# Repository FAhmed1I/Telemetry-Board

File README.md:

Telemetry Tracking PCB for automotive applications. Designed for testing of automotive projects

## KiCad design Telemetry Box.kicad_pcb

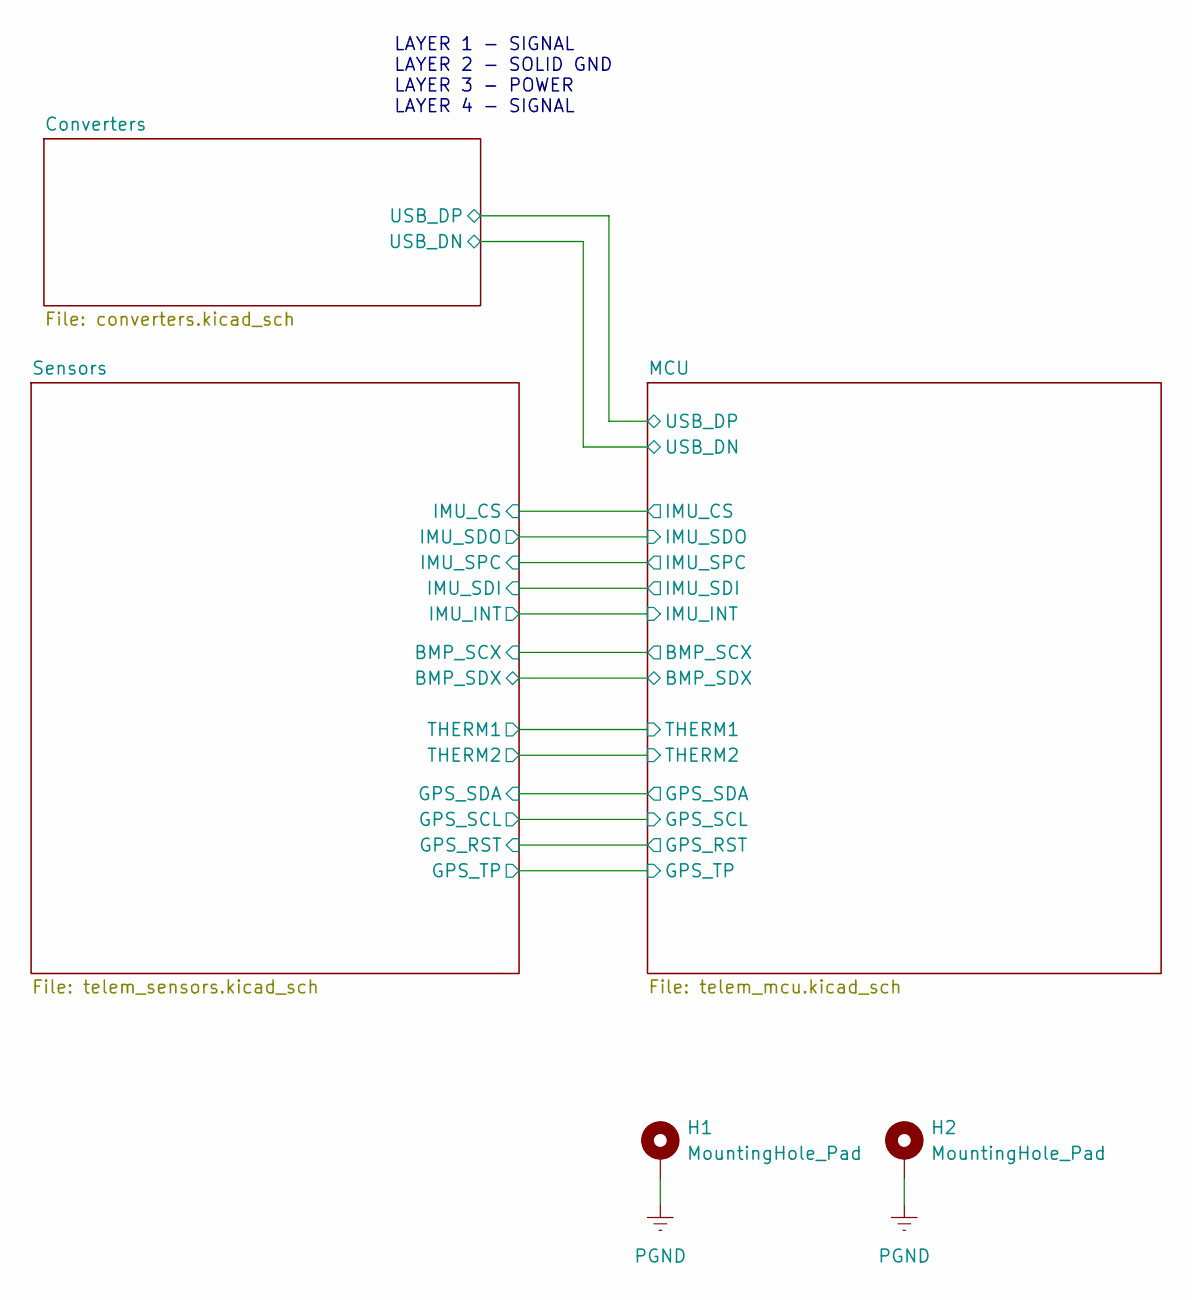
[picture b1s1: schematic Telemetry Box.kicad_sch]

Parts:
H1, H2: MountingHole_Pad; MountingHole_2.2mm_M2_DIN965_Pad

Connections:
PGND: H1.1 (1_1), H2.1 (1_1); also elsewhere on the board

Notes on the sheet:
LAYER 1 - SIGNAL LAYER 2 - SOLID GND LAYER 3 - POWER LAYER 4 - SIGNAL

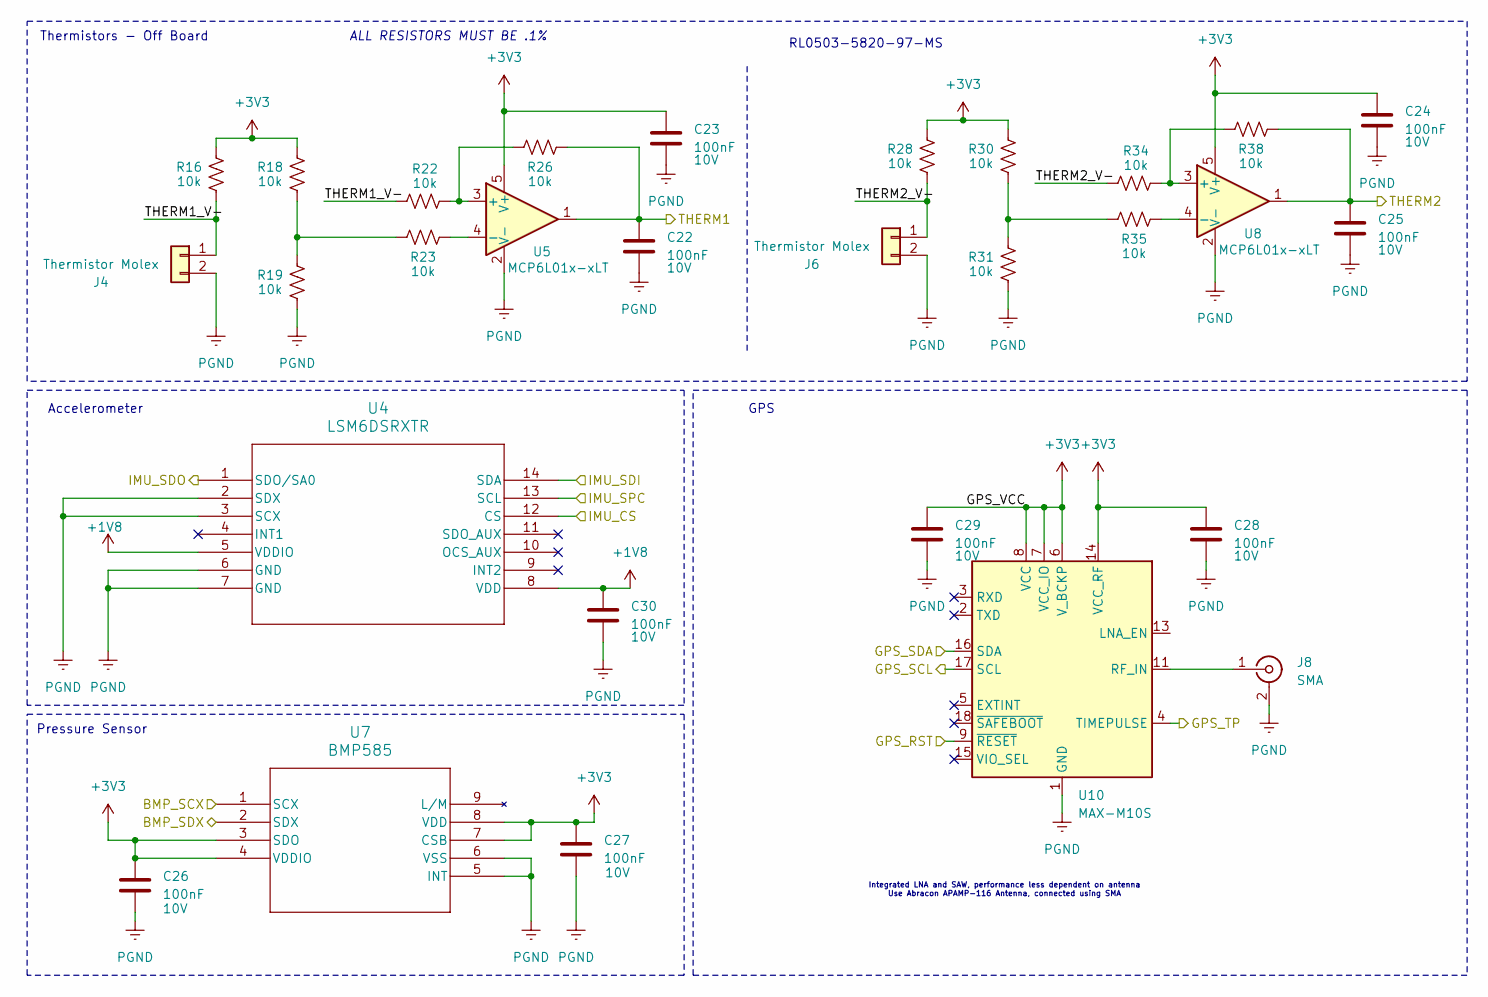
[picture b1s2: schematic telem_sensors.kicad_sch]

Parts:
C22, C23, C24, C25, C26, C27, C28, C29, C30: 100nF; C_0603_1608Metric; Voltage Rating 10V
J4, J6: Thermistor Molex; Molex_MicroClasp_55932-0230_1x02_P2.00mm_Vertical
J8: SMA; SMA_Amphenol_132289_EdgeMount
R16, R18, R19, R22, R23, R26, R28, R30, R31, R34, R35, R38: 10k; R_0603_1608Metric
U4: LSM6DSRXTR; LGA-14L_STM
U5, U8: MCP6L01x-xLT; SOT-353_SC-70-5
U7: BMP585; LGA9_BMP585_BOS
U10: MAX-M10S; ublox_MAX

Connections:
+1V8: C30.1, U4.5 (VDDIO), U4.8 (VDD); also elsewhere on the board
+3V3: C23.1, C24.1, C26.1, C27.1, C28.1, C29.1, R16.2, R18.2, R28.2, R30.2, U5.5 (V+), U7.3 (SDO), U7.4 (VDDIO), U7.7 (CSB), U7.8 (VDD), U8.5 (V+), U10.6 (V_BCKP), U10.7 (VCC_IO), U10.8 (VCC), U10.14 (VCC_RF); also elsewhere on the board
/MCU/BMP_SCX: U7.1 (SCX); also elsewhere on the board
/MCU/BMP_SDX: U7.2 (SDX); also elsewhere on the board
/MCU/GPS_RST: U10.9 (~RESET); also elsewhere on the board
/MCU/GPS_SCL: U10.17 (SCL); also elsewhere on the board
/MCU/GPS_SDA: U10.16 (SDA); also elsewhere on the board
/MCU/GPS_TP: U10.4 (TIMEPULSE); also elsewhere on the board
/MCU/IMU_CS: U4.12 (CS); also elsewhere on the board
/MCU/IMU_SDI: U4.14 (SDA); also elsewhere on the board
/MCU/IMU_SDO: U4.1 (SDO/SA0); also elsewhere on the board
/MCU/IMU_SPC: U4.13 (SCL); also elsewhere on the board
/MCU/THERM1: C22.1, R26.1, U5.1; also elsewhere on the board
/MCU/THERM2: C25.1, R38.1, U8.1; also elsewhere on the board
/Sensors/THERM1_V-: J4.1, R16.1, R22.2
/Sensors/THERM2_V-: J6.1, R28.1, R34.2
unnamed: J8.1 (In), U10.11 (RF_IN)
unnamed: R18.1, R19.2, R23.2
unnamed: R30.1, R31.2, R35.2
unnamed: R22.1, R26.2, U5.3 (+)
unnamed: R23.1, U5.4 (-)
unnamed: R34.1, R38.2, U8.3 (+)
unnamed: R35.1, U8.4 (-)
PGND: C22.2, C23.2, C24.2, C25.2, C26.2, C27.2, C28.2, C29.2, C30.2, J4.2, J6.2, J8.2 (Ext), R19.1, R31.1, U4.2 (SDX), U4.3 (SCX), U4.6 (GND), U4.7 (GND), U5.2 (V-), U7.5 (INT), U7.6 (VSS), U8.2 (V-), U10.1 (GND), U10.10 (GND), U10.12 (GND); also elsewhere on the board

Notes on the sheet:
RL0503-5820-97-MS
Thermistors - Off Board
Accelerometer
GPS
Integrated LNA and SAW, performance less dependent on antenna Use Abracon APAMP-116 Antenna, connected using SMA
ALL RESISTORS MUST BE .1%
Pressure Sensor

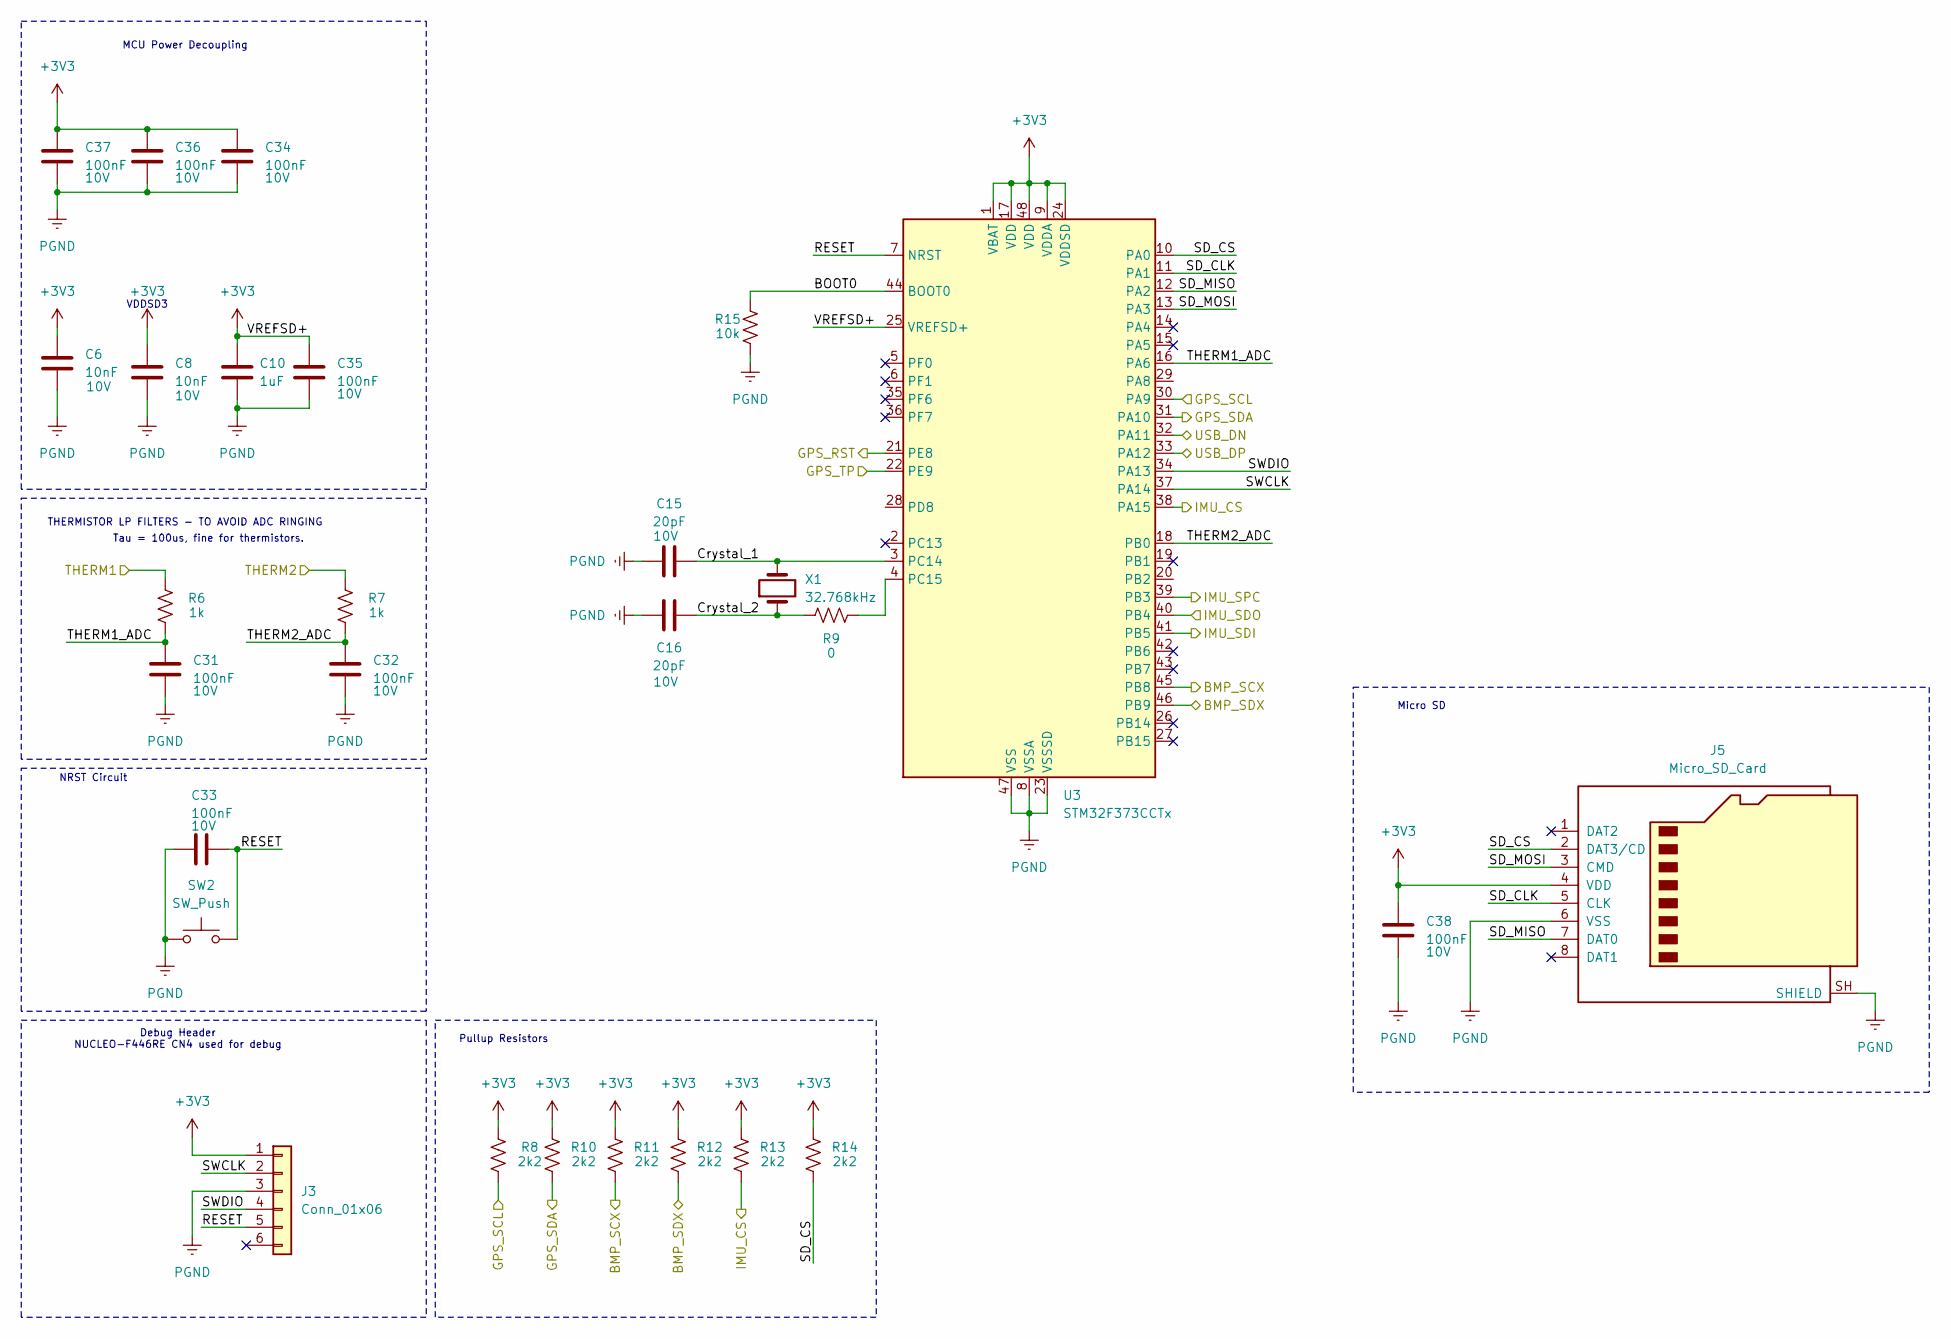
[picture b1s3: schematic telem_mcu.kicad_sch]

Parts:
C6, C8: 10nF; C_0603_1608Metric; Voltage Rating 10V
C10: 1uF; C_0603_1608Metric; Voltage Rating 10V
C15, C16: 20pF; C_0603_1608Metric; Voltage Rating 10V
C31, C32, C33, C34, C35, C36, C37, C38: 100nF; C_0603_1608Metric; Voltage Rating 10V
J3: Conn_01x06; PinHeader_1x06_P2.54mm_Vertical_SMD_Pin1Right
J5: Micro_SD_Card; AMPHENOL_10067099-200LF
R6, R7: 1k; R_0603_1608Metric
R8, R10, R11, R12, R13, R14: 2k2; R_0603_1608Metric
R9: 0; R_0603_1608Metric
R15: 10k; R_0603_1608Metric
SW2: SW_Push; SW_EVP-AWED4A
U3: STM32F373CCTx; LQFP-48_7x7mm_P0.5mm
X1: 32.768kHz; Crystal_SMD_3215-2Pin_3.2x1.5mm

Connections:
+3V3: C6.1, C8.1, C10.1, C34.1, C35.1, C36.1, C37.1, C38.1, J3.1, J5.4 (VDD), R8.2, R10.2, R11.2, R12.2, R13.2, R14.2, U3.1 (VBAT), U3.9 (VDDA), U3.17 (VDD), U3.24 (VDDSD), U3.25 (VREFSD+), U3.48 (VDD); also elsewhere on the board
/Converters/USB_DN: U3.32 (PA11); also elsewhere on the board
/Converters/USB_DP: U3.33 (PA12); also elsewhere on the board
/MCU/BMP_SCX: R11.1, U3.45 (PB8); also elsewhere on the board
/MCU/BMP_SDX: R12.1, U3.46 (PB9); also elsewhere on the board
/MCU/BOOT0: R15.2, U3.44 (BOOT0)
/MCU/Crystal_1: C15.2, U3.3 (PC14), X1.2
/MCU/Crystal_2: C16.2, R9.1, X1.1
/MCU/GPS_RST: U3.21 (PE8); also elsewhere on the board
/MCU/GPS_SCL: R8.1, U3.30 (PA9); also elsewhere on the board
/MCU/GPS_SDA: R10.1, U3.31 (PA10); also elsewhere on the board
/MCU/GPS_TP: U3.22 (PE9); also elsewhere on the board
/MCU/IMU_CS: R13.1, U3.38 (PA15); also elsewhere on the board
/MCU/IMU_SDI: U3.41 (PB5); also elsewhere on the board
/MCU/IMU_SDO: U3.40 (PB4); also elsewhere on the board
/MCU/IMU_SPC: U3.39 (PB3); also elsewhere on the board
/MCU/RESET: C33.2, J3.5, SW2.2, U3.7 (NRST)
/MCU/SD_CLK: J5.5 (CLK), U3.11 (PA1)
/MCU/SD_CS: J5.2 (DAT3/CD), R14.1, U3.10 (PA0)
/MCU/SD_MISO: J5.7 (DAT0), U3.12 (PA2)
/MCU/SD_MOSI: J5.3 (CMD), U3.13 (PA3)
/MCU/SWCLK: J3.2, U3.37 (PA14)
/MCU/SWDIO: J3.4, U3.34 (PA13)
/MCU/THERM1: R6.2; also elsewhere on the board
/MCU/THERM1_ADC: C31.1, R6.1, U3.16 (PA6)
/MCU/THERM2: R7.2; also elsewhere on the board
/MCU/THERM2_ADC: C32.1, R7.1, U3.18 (PB0)
unnamed: R9.2, U3.4 (PC15)
PGND: C6.2, C8.2, C10.2, C15.1, C16.1, C31.2, C32.2, C33.1, C34.2, C35.2, C36.2, C37.2, C38.2, J3.3, J5.6 (VSS), J5.SH (SHIELD), R15.1, SW2.1, U3.8 (VSSA), U3.23 (VSSSD), U3.47 (VSS); also elsewhere on the board

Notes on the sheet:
Debug Header NUCLEO-F446RE CN4 used for debug
VDDSD3
THERMISTOR LP FILTERS - TO AVOID ADC RINGING
MCU Power Decoupling
Pullup Resistors
Micro SD
NRST Circuit
Tau = 100us, fine for thermistors.

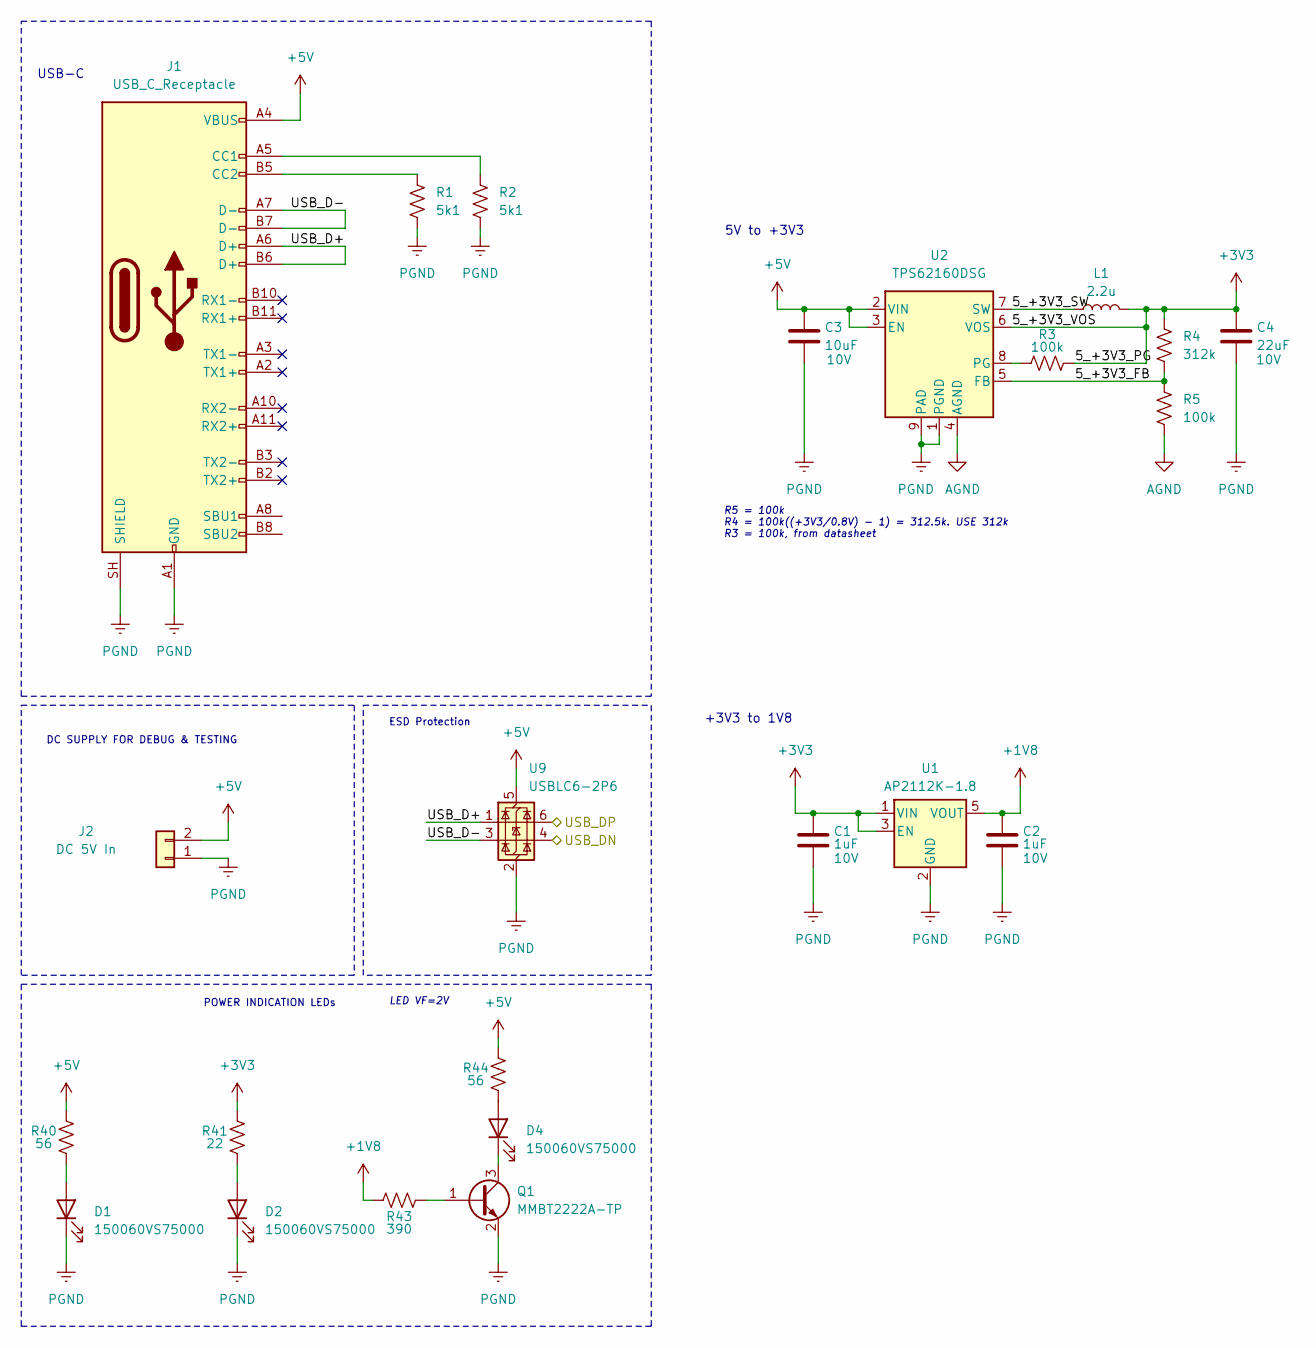
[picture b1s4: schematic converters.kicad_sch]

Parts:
C1, C2: 1uF; C_0603_1608Metric; Voltage Rating 10V
C3: 10uF; C_0603_1608Metric; Voltage Rating 10V
C4: 22uF; C_0603_1608Metric; Voltage Rating 10V
D1, D2, D4: 150060VS75000; LED_0603_1608Metric
J1: USB_C_Receptacle; USB_C_Receptacle_Amphenol_12401610E4-2A
J2: DC 5V In; PinHeader_1x02_P2.00mm_Vertical
L1: 2.2u; L_1008_2520Metric
Q1: MMBT2222A-TP; SOT-23-3
R1, R2: 5k1; R_0805_2012Metric_Pad1.20x1.40mm_HandSolder
R3, R5: 100k; R_0805_2012Metric_Pad1.20x1.40mm_HandSolder
R4: 312k; R_0805_2012Metric_Pad1.20x1.40mm_HandSolder
R40, R44: 56; R_0603_1608Metric
R41: 22; R_0603_1608Metric
R43: 390; R_0603_1608Metric
U1: AP2112K-1.8; SOT-23-5
U2: TPS62160DSG; WSON-8-1EP_2x2mm_P0.5mm_EP0.9x1.6mm_ThermalVias
U9: USBLC6-2P6; SOT-666

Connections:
+1V8: C2.1, R43.2, U1.5 (VOUT); also elsewhere on the board
+3V3: C1.1, C4.1, L1.2, R3.2, R4.1, R41.2, U1.1 (VIN), U1.3 (EN), U2.6 (VOS); also elsewhere on the board
+5V: C3.1, J1.A4 (VBUS), J1.A9 (VBUS), J1.B4 (VBUS), J1.B9 (VBUS), J2.2, R40.2, R44.2, U2.2 (VIN), U2.3 (EN), U9.5 (VBUS)
/Converters/5_+3V3_FB: R4.2, R5.1, U2.5 (FB)
/Converters/5_+3V3_SW: L1.1, U2.7 (SW)
/Converters/USB_D+: J1.A6 (D+), J1.B6 (D+), U9.1 (I/O1)
/Converters/USB_D-: J1.A7 (D-), J1.B7 (D-), U9.3 (I/O2)
/Converters/USB_DN: U9.4 (I/O2); also elsewhere on the board
/Converters/USB_DP: U9.6 (I/O1); also elsewhere on the board
AGND: R5.2, U2.4 (AGND)
unnamed: D1.2 (A), R40.1
unnamed: D2.2 (A), R41.1
unnamed: D4.2 (A), R44.1
unnamed: D4.1 (K), Q1.3 (C)
unnamed: J1.A5 (CC1), R2.1
unnamed: J1.B5 (CC2), R1.1
unnamed: Q1.1 (B), R43.1
unnamed: R3.1, U2.8 (PG)
PGND: C1.2, C2.2, C3.2, C4.2, D1.1 (K), D2.1 (K), J1.A1 (GND), J1.A12 (GND), J1.B1 (GND), J1.B12 (GND), J1.SH (SHIELD), J2.1, Q1.2 (E), R1.2, R2.2, U1.2 (GND), U2.1 (PGND), U2.9 (PAD), U9.2 (GND); also elsewhere on the board

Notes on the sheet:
+3V3 to 1V8
R5 = 100k R4 = 100k((+3V3/0.8V) - 1) = 312.5k. USE 312k R3 = 100k, from datasheet
LED VF=2V
USB-C
5V to +3V3
DC SUPPLY FOR DEBUG & TESTING
POWER INDICATION LEDs
ESD Protection

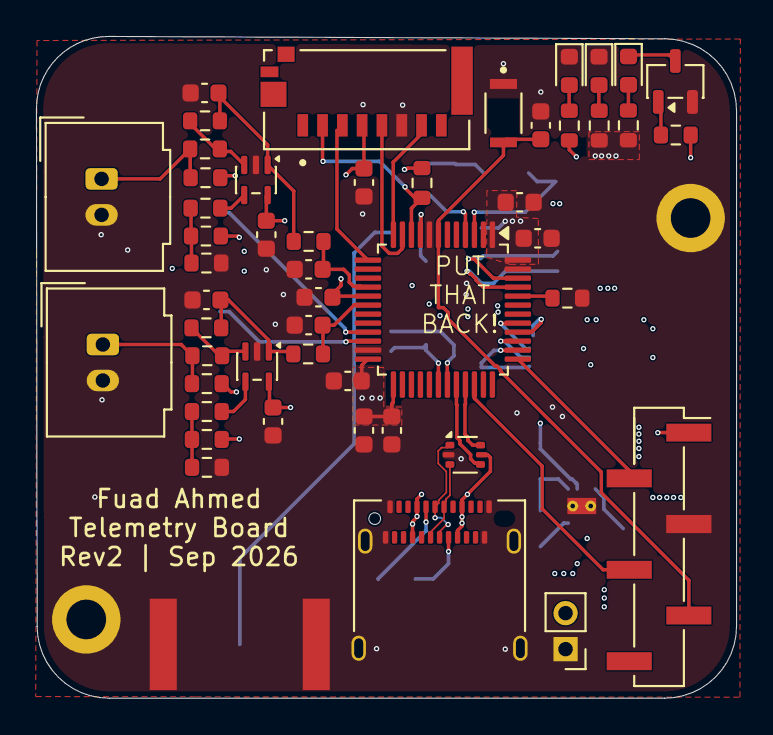
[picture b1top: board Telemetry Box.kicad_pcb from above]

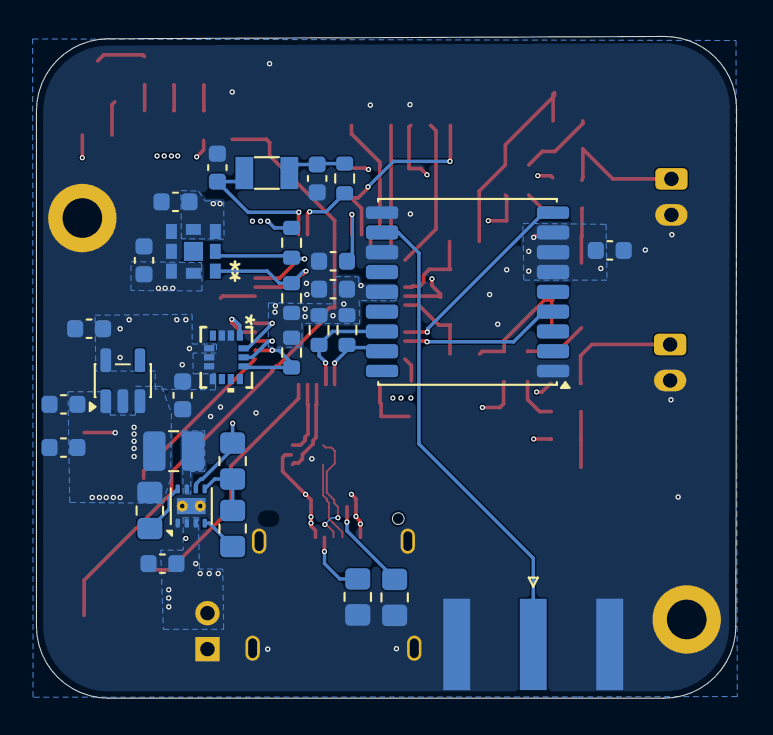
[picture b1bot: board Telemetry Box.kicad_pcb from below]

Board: 4 copper layers, 38.9 x 36.8 mm, 82 parts (31 on the bottom side), 53 nets.

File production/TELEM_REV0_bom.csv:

Designator,Footprint,Quantity,Value,LCSC Part #
"C1, C2",0805,2,1u,
C10,0603,1,1uF,
"C11, C20, C22, C24, C28, C30, C5, C7, C9",0603,9,100nF,
"C12, C17, C21, C26, C27, C32, C33",0805,7,100nF,
"C15, C16",0603,2,20pF,
C3,0805,1,10u,
C4,0805,1,22u,
"C6, C8",0603,2,10nF,
"D1, D2, D4",0603,3,150060VS75000,
J1,USB_C_Receptacle_Amphenol_12401610E4-2A,1,USB_C_Receptacle,
J2,PinHeader_1x02_P2.00mm_Vertical,1,DC 5V In,
J3,PinHeader_1x06_P2.54mm_Vertical_SMD_Pin1Right,1,Conn_01x06,
"J4, J6",Molex_MicroClasp_55935-0230_1x02_P2.00mm_Horizontal,2,Thermistor Molex,
J8,SMA_Amphenol_132289_EdgeMount,1,SMA,
L1,1008,1,2.2u,
Q1,SOT-23-3,1,MMBT2222A-TP,
"R1, R2",0805,2,5k1,
"R15, R16, R18, R19, R22, R23, R26, R28, R30, R31, R34, R35, R38",0603,13,10k,
"R3, R5",0805,2,100k,
R4,0805,1,312k,
"R40, R44",0603,2,56,
R41,0603,1,22,
R43,0603,1,390,
"R6, R7",0603,2,1k,
R9,0603,1,0,
SW2,SW_EVP-AWED4A,1,SW_Push,
SW3,SWITCH_1SCQN,1,SW_SPDT,
U1,SOT-23-5,1,AP2112K-1.8,
U10,ublox_MAX,1,MAX-M10S,
U2,WSON-8-1EP_2x2mm_P0.5mm_EP0.9x1.6mm_ThermalVias,1,TPS62160DSG,
U3,LQFP-48_7x7mm_P0.5mm,1,STM32F373CCTx,
U4,LGA-14L_STM,1,LSM6DSRXTR,
"U5, U8",SOT-353_SC-70-5,2,MCP6L01x-xLT,
U7,LGA9_BMP585_BOS,1,BMP585,
X1,Crystal_SMD_3215-2Pin_3.2x1.5mm,1,32.768kHz,
